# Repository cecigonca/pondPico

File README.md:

# Atividade Ponderada PCB - Semana 6
Atividade Ponderada - Placa de circuito impresso com Raspberry Pi Pico

Este repositório contém uma atividade que tem por objetivo desenvolver uma placa de circuito impresso capaz de receber um Raspberry Pi Pico W encaixado utilizando um dispositivo conector, além de um hardware para acionar uma interface de potência (relé e transistor), um dispositivo sinalizador (LED ou Buzzer) e um dispositivo de entrada (analógico ou digital). Esta placa deverá ser construída utilizando o software de CAD para placas eletrônicas utilizado no módulo vigente, além de prototipada utilizando as ferramentas disponíveis no laboratório da instituição. Espera-se que os estudantes possam compreender o processo de construção de placas auxiliares de circuito eletrônico.

No meu circuito foram utilizados 2 LEDs, 2 resistores, 1 transistor e 1 conector

## Pastas e Arquivos
`/imagens`

- `esquematico.png`: Imagem do esquemático do circuito.
- `pcb.png`: Imagem da placa de circuito impresso (PCB).
- `representacao.png`: Imagem representativa de algum aspecto do projeto.

`/ponderada-pico`: Pasta do projeto contendo os arquivos do KiCad.

- `ponderada-pico.kicad_pcb`: Arquivo do layout da PCB.
- `ponderada-pico.kicad_prl`: Arquivo de configurações do projeto.
- `ponderada-pico.kicad_pro`: Arquivo principal do projeto que agrega todos os elementos.
- `ponderada-pico.kicad_sch`: Arquivo do esquemático do circuito.
- `/ponderada-pico-backups`: Pasta é usada pelo KiCad para armazenar arquivos salvos automaticament
  
## Imagens
### Esquemático

### PCB

### Visualização 3D

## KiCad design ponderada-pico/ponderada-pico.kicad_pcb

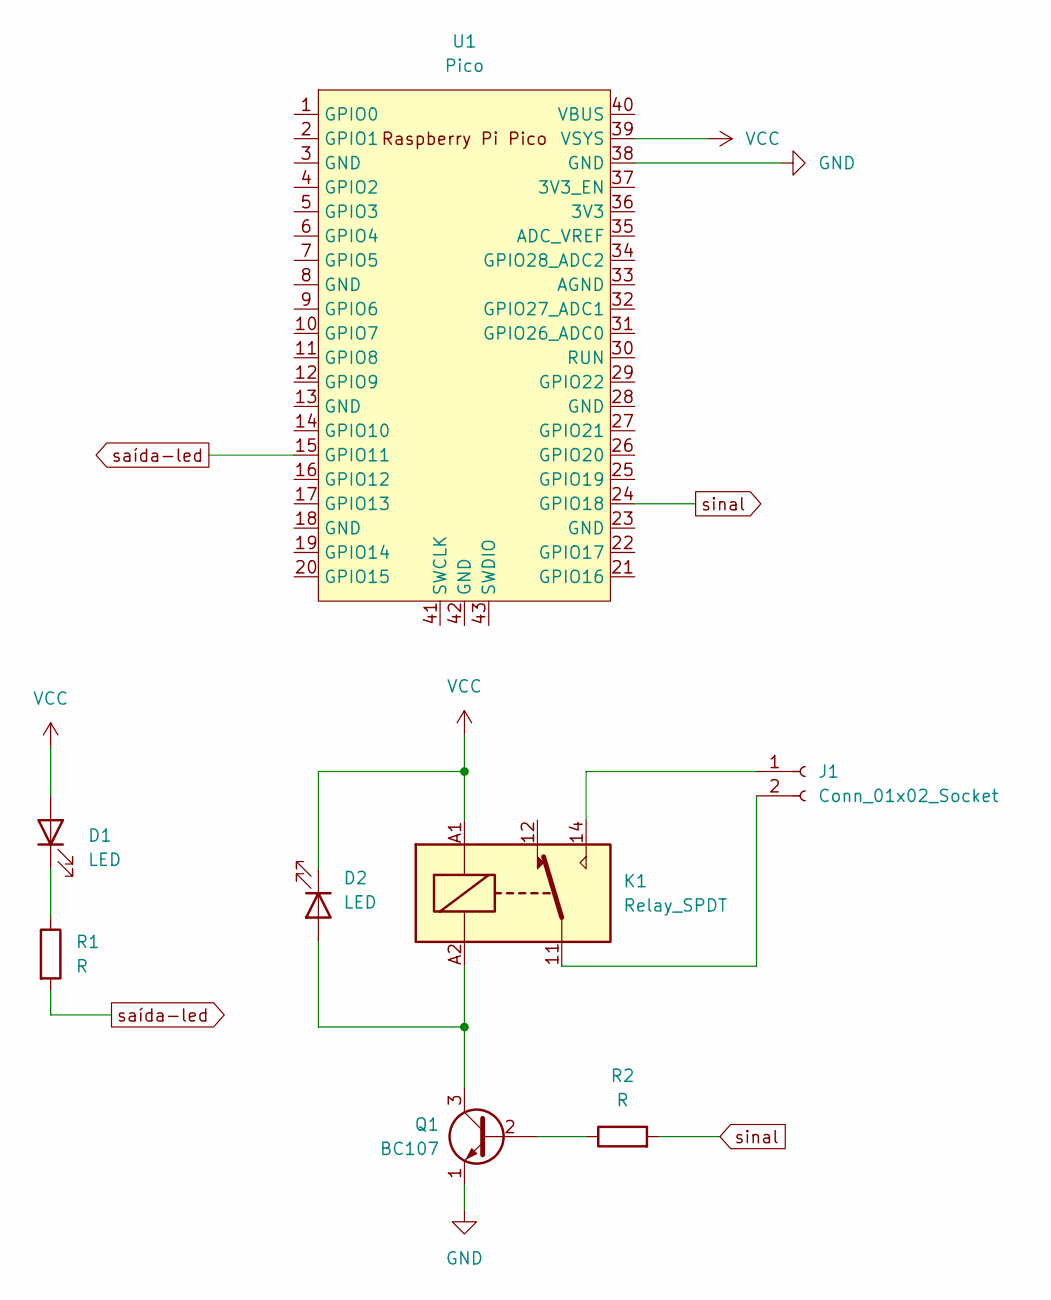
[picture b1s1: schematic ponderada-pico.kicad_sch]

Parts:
D1, D2: LED; LED_0603_1608Metric_Pad1.05x0.95mm_HandSolder
J1: Conn_01x02_Socket; JST_EH_B2B-EH-A_1x02_P2.50mm_Vertical
K1: Relay_SPDT; Relay_SPDT_Schrack-RP-II-1-FormC_RM3.5mm
Q1: BC107; TO-18-3
R1, R2: R; R_0603_1608Metric
U1: Pico; RPi_Pico_SMD_TH

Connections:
GND: Q1.1 (E), U1.38 (GND)
unnamed: D1.1 (K), R1.1
unnamed: D2.2 (A), K1.A2, Q1.3 (C)
unnamed: J1.1, K1.14
unnamed: J1.2, K1.11
unnamed: Q1.2 (B), R2.1
VCC: D1.2 (A), D2.1 (K), K1.A1, U1.39 (VSYS)
saída-led: R1.2, U1.15 (GPIO11)
sinal: R2.2, U1.24 (GPIO18)

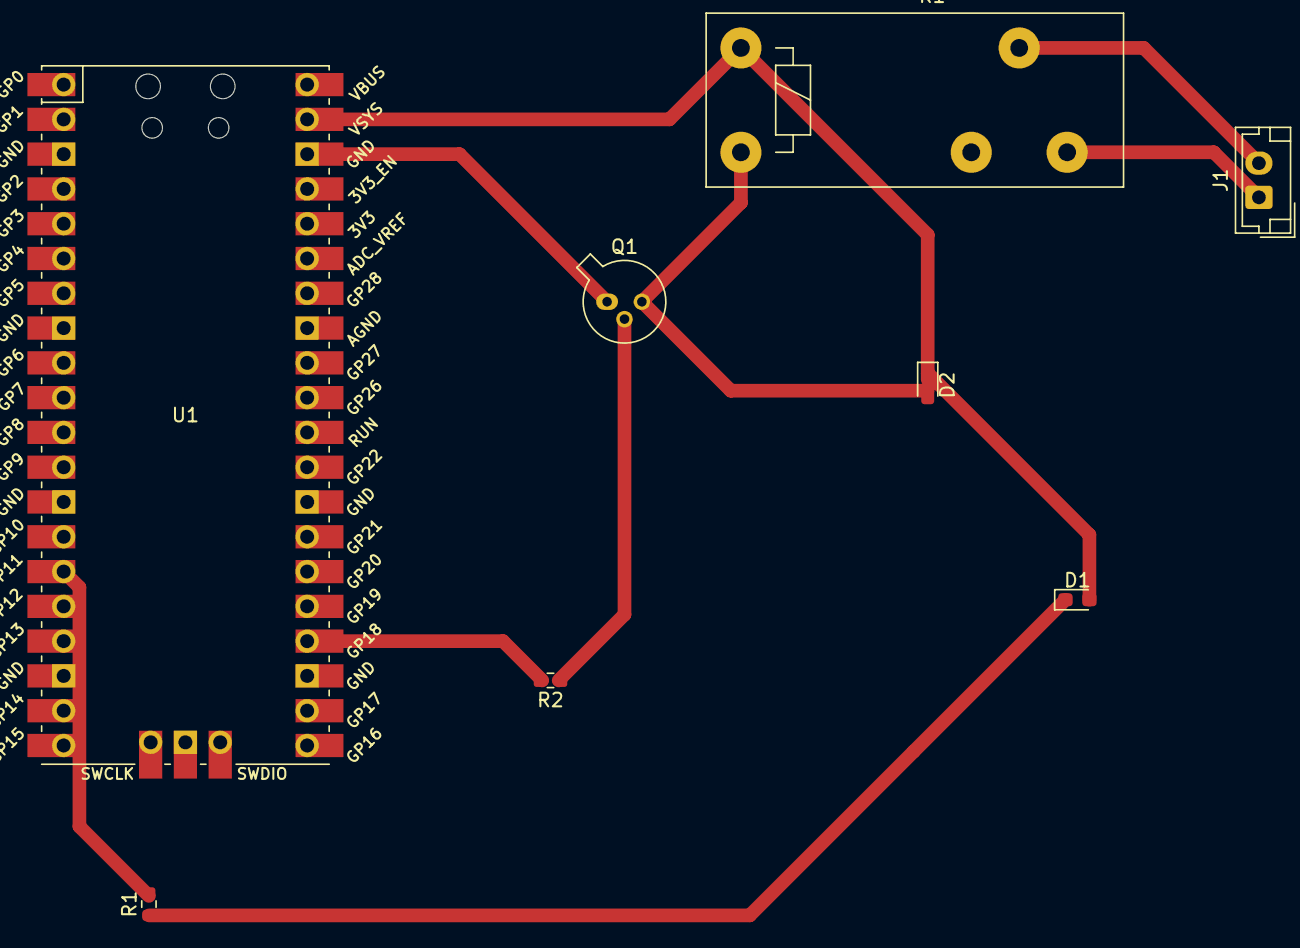
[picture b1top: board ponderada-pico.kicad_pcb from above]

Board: 2 copper layers, 8 parts (0 on the bottom side), 9 nets.

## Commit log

2024-04-01 Material KiCad
    Circuito e PCB desenvolvidos no KiCad
2024-04-01 Delete
    Caminho errado
2024-04-01 Adição de imagens
    Criação da pasta "Imagens" para armazenamento dos prints de tela do esquemático e PCB.
2024-04-01 Material KiCad
    Importação do que foi desenvolvido no Kicad, mais especificamente o esquemático e o PCB do meu circuíto.
2024-04-01 Update README.md
    Descrição da atividade
2024-04-01 Imagens no README
2024-04-01 Remoção das imagens
2024-04-01 Update README
    Adição de imagens no README
2024-04-01 Update README.md
    Documentação da estrutura de pastas e arquivos
